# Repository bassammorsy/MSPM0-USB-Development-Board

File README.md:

# MSPM0 USB Development Board

A 2-layer development board built around the Texas Instruments MSPM0
microcontroller, designed for prototyping and peripheral interfacing
via USB-C.

## Features
- TI MSPM0 microcontroller
- USB-C connector with CH340 USB-to-UART bridge for serial communication
- Manually routed USB differential pair with impedance matching
- Crystal oscillator with datasheet-compliant layout guidelines
- I2C header for connecting external sensors and peripherals
- Hardware reset circuit via NRST line
- Decoupling capacitors on all IC power pins
- 3.3V power regulation from 5V VBUS
- Dual-layer GND copper pour
- Mounting holes at all four corners

## Specs
- Layers: 2
- Pads: 205
- Nets: 61
- Track Segments: 328

## Tools
- KiCad 9

## Files
- `/gerbers` — fabrication-ready Gerber and drill files
- `MSPM0.kicad_pcb` — PCB layout
- `MSPM0.kicad_sch` — schematic
- `MSPM0.kicad_pro` — project file

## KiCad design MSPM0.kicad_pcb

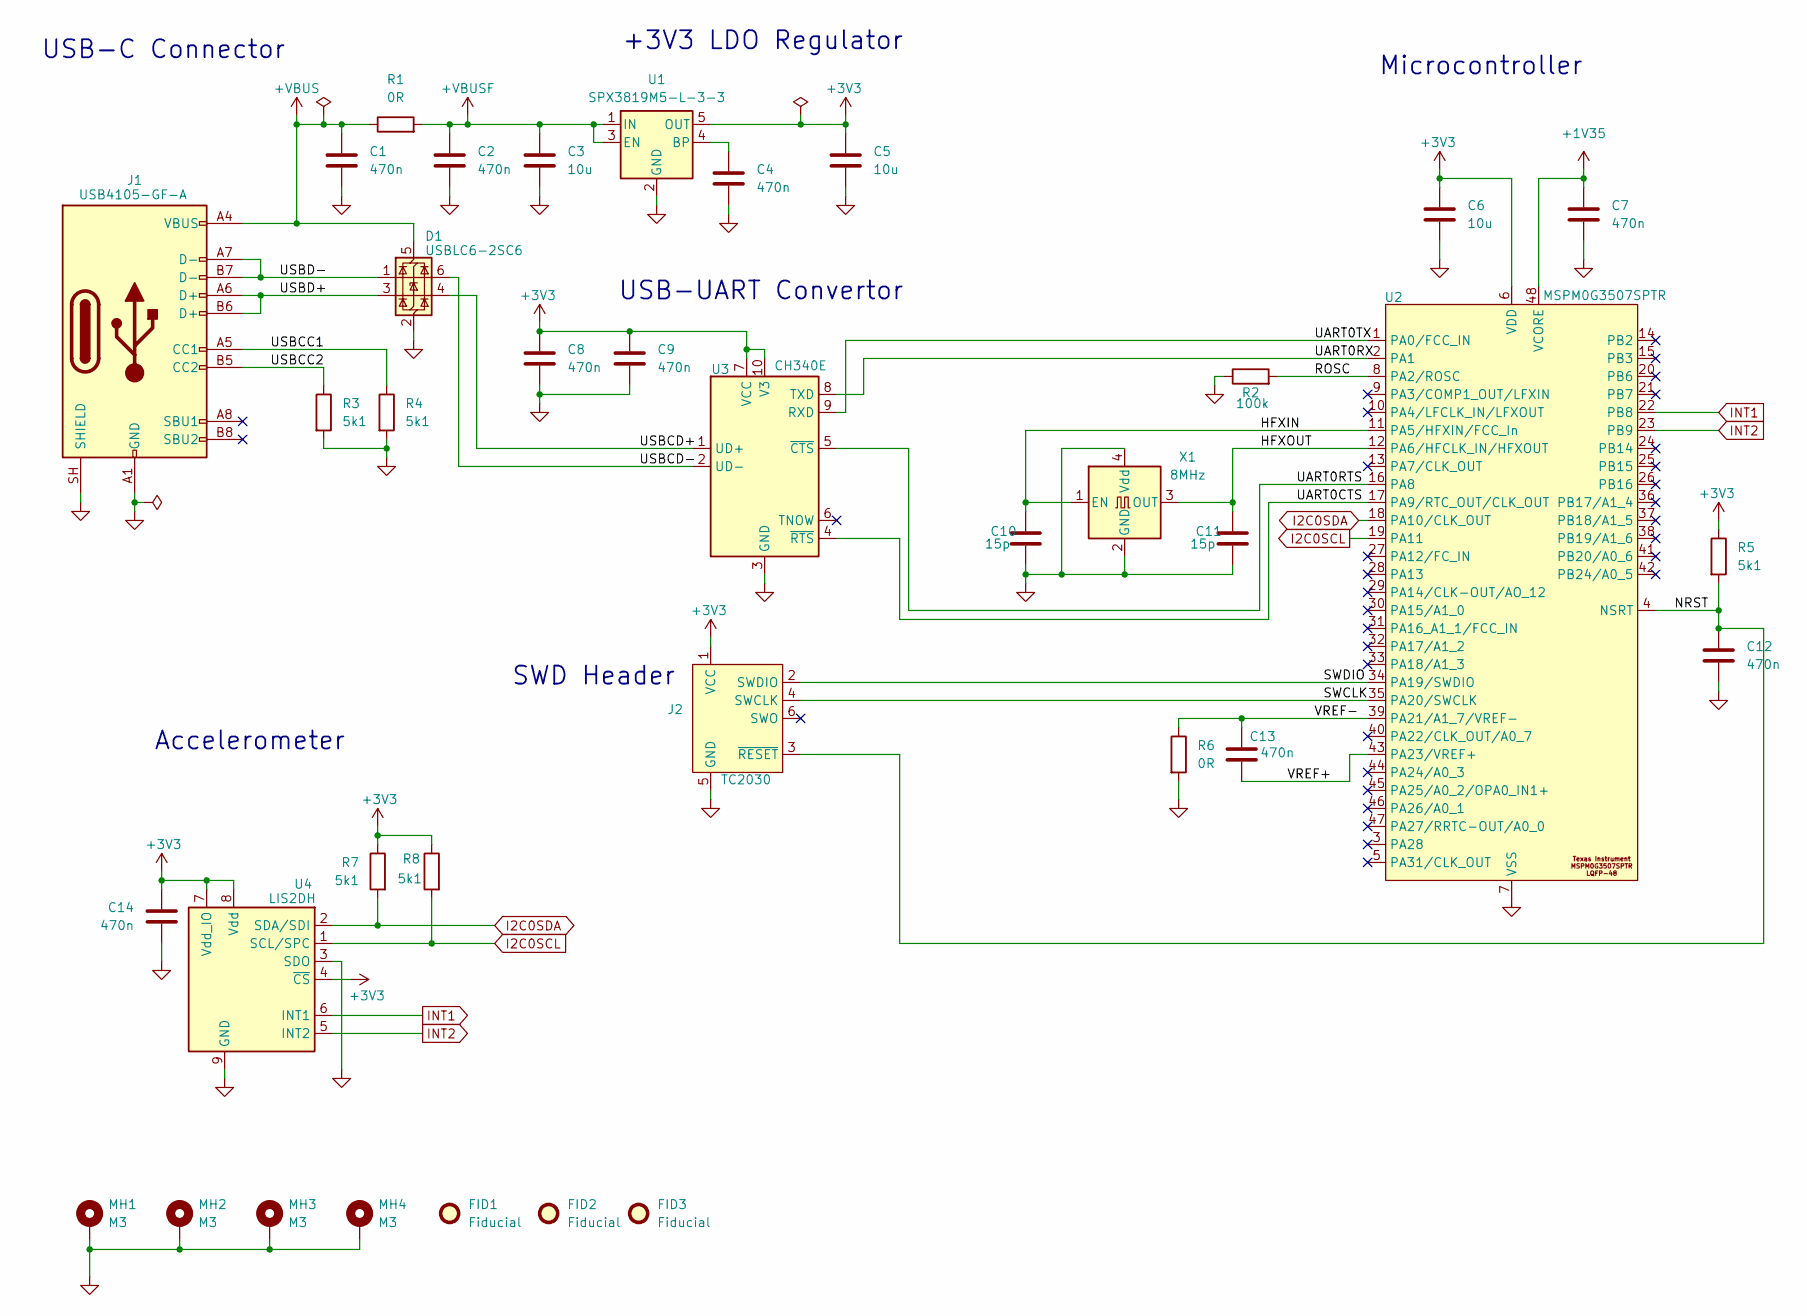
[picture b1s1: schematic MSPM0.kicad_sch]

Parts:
C1, C2, C4, C8, C9: 470n; C_0805_2012Metric
C3, C5, C6: 10u; C_0805_2012Metric
C7, C12, C13, C14: 470n; C_0603_1608Metric
C10, C11: 15p; C_0603_1608Metric
D1: USBLC6-2SC6; SOT-23-6
FID1, FID2, FID3: Fiducial; Fiducial_1mm_Mask2mm
J1: USB4105-GF-A; USB_C_Receptacle_GCT_USB4105-xx-A_16P_TopMnt_Horizontal
J2: TC2030; Tag-Connect_TC2030-IDC-FP_2x03_P1.27mm_Vertical
MH1, MH2, MH3, MH4: M3; MountingHole_3.2mm_M3_Pad_Via
R1, R6: 0R; C_0603_1608Metric
R2: 100k; C_0603_1608Metric
R3, R4, R5, R7, R8: 5k1; C_0603_1608Metric
U1: SPX3819M5-L-3-3; SOT-23-5
U2: MSPM0G3507SPTR; LQFP-48_7x7mm_P0.5mm; Part Number MSPM0G3507SPTR
U3: CH340E; MSOP-10_3x3mm_P0.5mm
U4: LIS2DH; LGA-14_2x2mm_P0.35mm_LayoutBorder3x4y
X1: 8MHz; Oscillator_SMD_Abracon_ASE-4Pin_3.2x2.5mm

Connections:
+1V35: C7.1, U2.48 (VCORE)
+3V3: C5.1, C6.1, C8.1, C9.1, C14.1, J2.1 (VCC), R5.1, R7.1, R8.1, U1.5 (OUT), U2.6 (VDD), U3.7 (VCC), U3.10 (V3), U4.4 (~CS), U4.7 (Vdd_IO), U4.8 (Vdd)
+VBUS: C1.1, D1.5 (VBUS), J1.A4 (VBUS), J1.A9 (VBUS), J1.B4 (VBUS), J1.B9 (VBUS), R1.1
+VBUSF: C2.1, C3.1, R1.2, U1.1 (IN), U1.3 (EN)
/HFXIN: C10.1, U2.11 (PA5/HFXIN/FCC_In), X1.1 (EN)
/HFXOUT: C11.1, U2.12 (PA6/HFCLK_IN/HFXOUT), X1.3 (OUT)
/NRST: C12.1, J2.3 (~RESET), R5.2, U2.4 (NSRT)
/ROSC: R2.2, U2.8 (PA2/ROSC)
/SWCLK: J2.4 (SWCLK), U2.35 (PA20/SWCLK)
/SWDIO: J2.2 (SWDIO), U2.34 (PA19/SWDIO)
/UART0CTS: U2.17 (PA9/RTC_OUT/CLK_OUT), U3.4 (~RTS)
/UART0RTS: U2.16 (PA8), U3.5 (~CTS)
/UART0RX: U2.2 (PA1), U3.8 (TXD)
/UART0TX: U2.1 (PA0/FCC_IN), U3.9 (RXD)
/USBCC1: J1.A5 (CC1), R4.1
/USBCC2: J1.B5 (CC2), R3.1
/USBCD+: D1.4 (I/O2), U3.1 (UD+)
/USBCD-: D1.6 (I/O1), U3.2 (UD-)
/USBD+: D1.3 (I/O2), J1.A6 (D+), J1.B6 (D+)
/USBD-: D1.1 (I/O1), J1.A7 (D-), J1.B7 (D-)
/VREF+: C13.2, U2.43 (PA23/VREF+)
/VREF-: C13.1, R6.1, U2.39 (PA21/A1_7/VREF-)
GND: C1.2, C2.2, C3.2, C4.2, C5.2, C6.2, C7.2, C8.2, C9.2, C10.2, C11.2, C12.2, C14.2, D1.2 (GND), J1.A1 (GND), J1.A12 (GND), J1.B1 (GND), J1.B12 (GND), J1.SH (SHIELD), J2.5 (GND), MH1.1 (1_1), MH2.1 (1_1), MH3.1 (1_1), MH4.1 (1_1), R2.1, R3.2, R4.2, R6.2, U1.2 (GND), U2.7 (VSS), U3.3 (GND), U4.3 (SDO), U4.9 (GND), X1.2 (GND), X1.4 (Vdd)
I2C0SCL: R8.2, U2.19 (PA11), U4.1 (SCL/SPC)
I2C0SDA: R7.2, U2.18 (PA10/CLK_OUT), U4.2 (SDA/SDI)
INT1: U2.22 (PB8), U4.6 (INT1)
INT2: U2.23 (PB9), U4.5 (INT2)
unnamed: C4.1, U1.4 (BP)
unnamed: U4.10 (GND), U4.11 (GND), U4.12 (GND), U4.13 (GND), U4.14 (GND)

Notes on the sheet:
USB-UART Convertor
Accelerometer
USB-C Connector
Microcontroller
SWD Header
+3V3 LDO Regulator

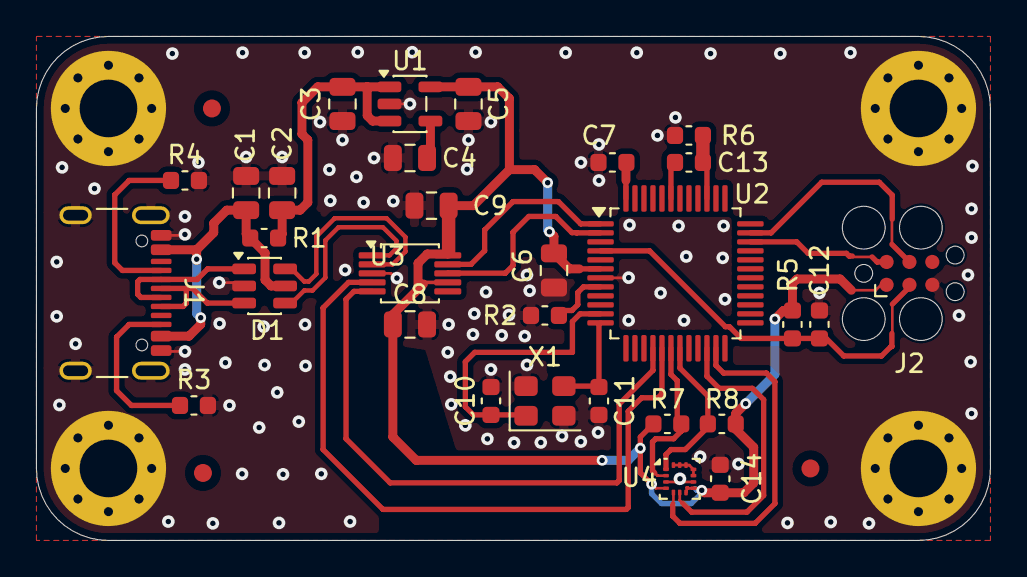
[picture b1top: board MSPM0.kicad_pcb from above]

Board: 2 copper layers, 53.0 x 28.0 mm, 37 parts (0 on the bottom side), 29 nets.

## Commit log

2026-04-26 KiCad project files and Gerbers
2026-04-26 Updated README
    Added detailed description, features, specs, tools, and files for the MSPM0 USB Development Board.
2026-04-28 Update README
    Removed specific impedance value from USB differential pair description.
2026-04-29 Screenshot upload
